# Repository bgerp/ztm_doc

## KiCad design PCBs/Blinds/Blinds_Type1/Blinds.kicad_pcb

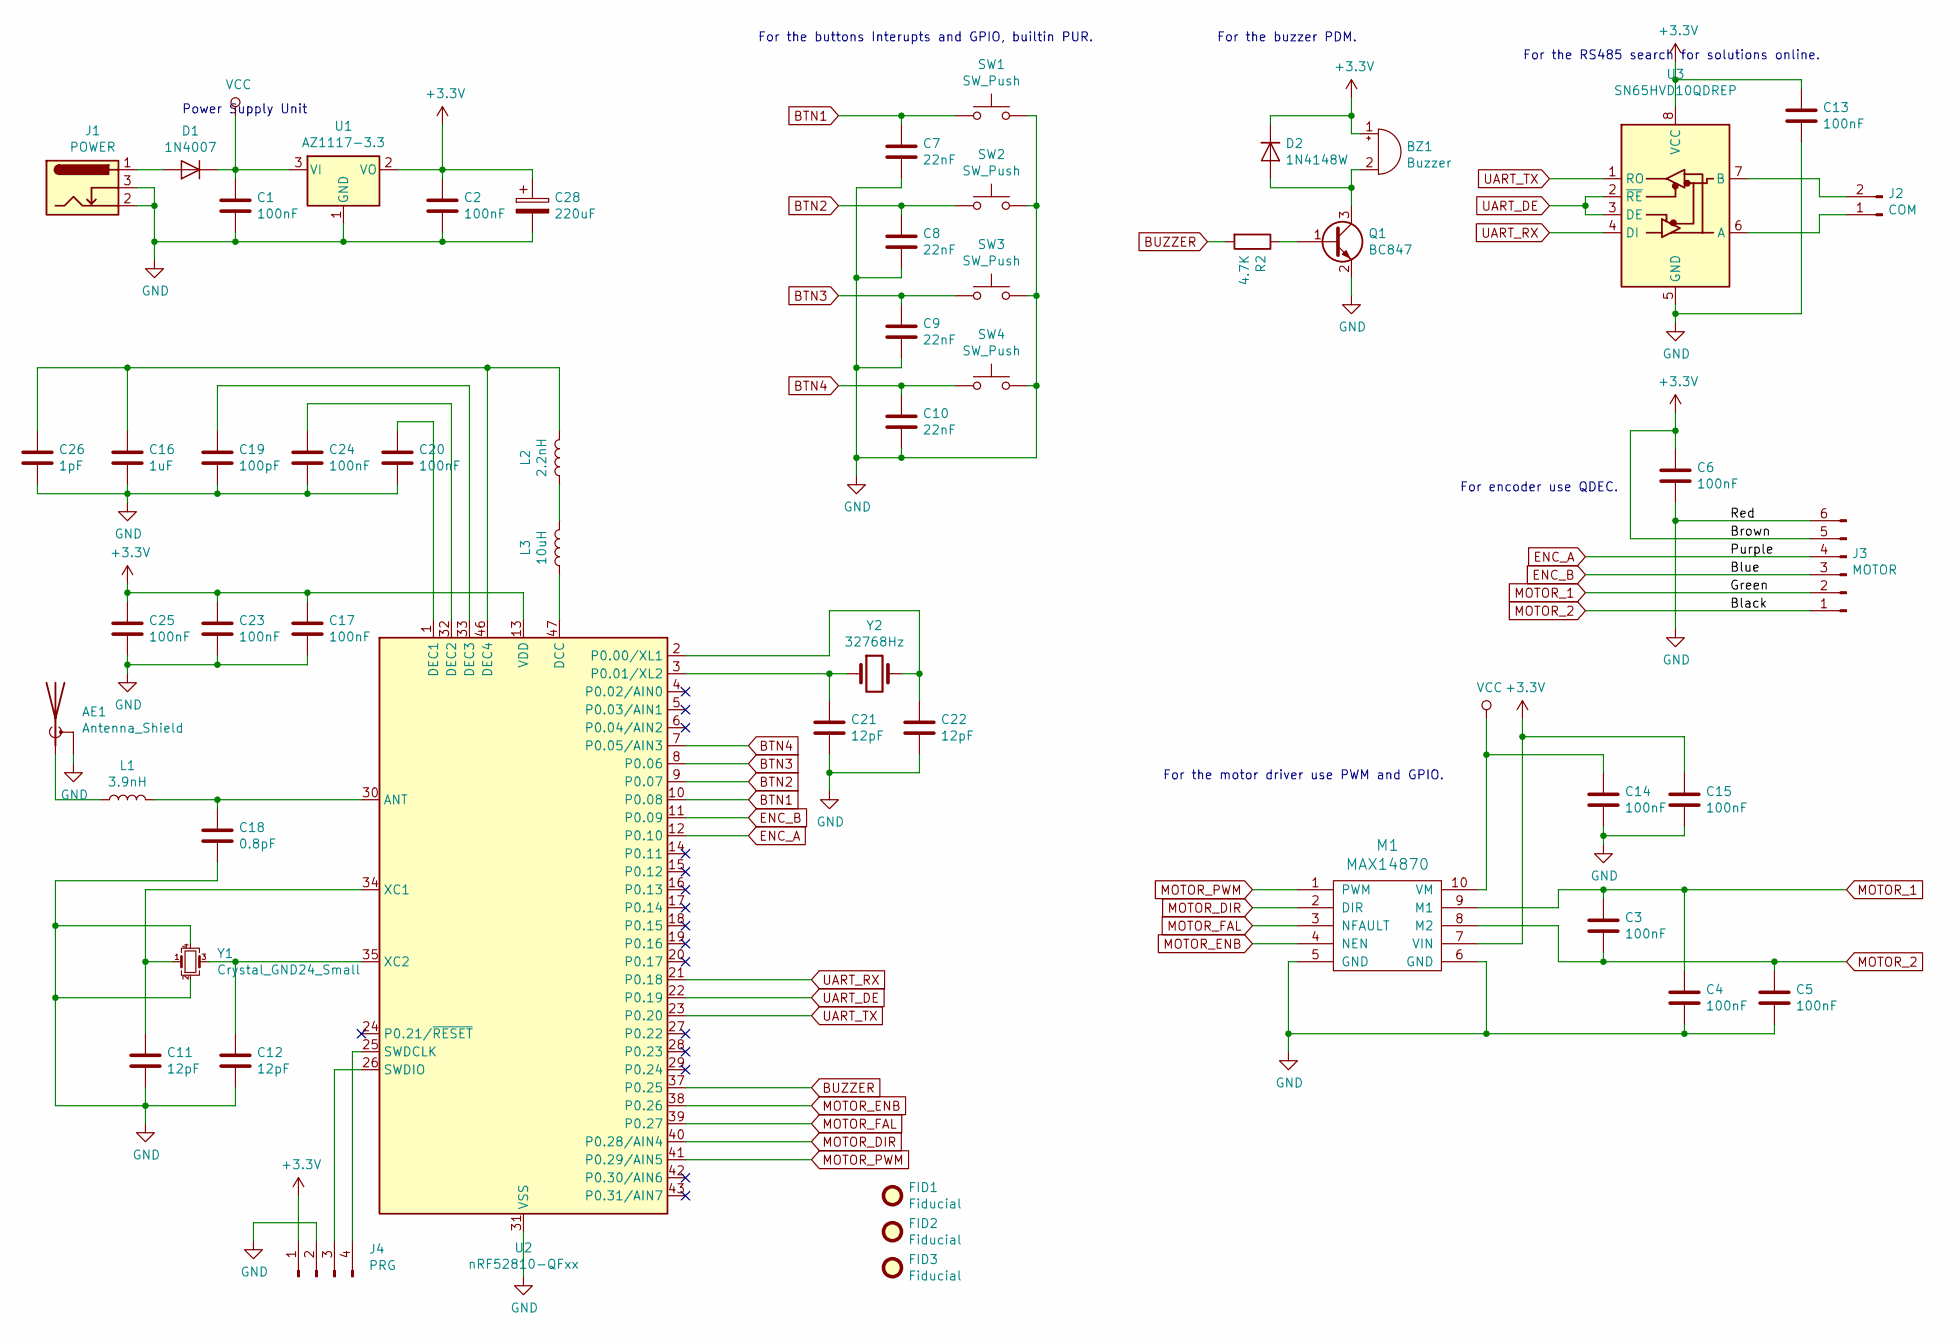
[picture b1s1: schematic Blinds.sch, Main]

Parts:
AE1: Antenna_Shield; Texas_SWRA117D_2.4GHz_Left
BZ1: Buzzer; MagneticBuzzer_Kingstate_KCG0601
C1, C2, C3, C4, C5, C6, C13, C14, C15, C23: 100nF; C_0603_1608Metric
C7, C8, C9, C10: 22nF; C_0603_1608Metric
C11, C12, C21, C22: 12pF; C_0402_1005Metric
C16: 1uF; C_0603_1608Metric
C17, C20, C24, C25: 100nF; C_0402_1005Metric
C18: 0.8pF; C_0402_1005Metric
C19: 100pF; C_0402_1005Metric
C26: 1pF; C_0402_1005Metric
C28: 220uF; CP_Elec_6.3x7.7
D1: 1N4007; D_SMA
D2: 1N4148W; D_SOD-123
FID1, FID2, FID3: Fiducial; Fiducial_0.5mm_Mask1mm
J1: POWER; BarrelJack_Horizontal
J2: COM; PinHeader_1x02_P2.54mm_Vertical
J3: MOTOR; JST_PH_B6B-PH-K_1x06_P2.00mm_Vertical
J4: PRG; PinHeader_1x04_P2.54mm_Vertical
L1: 3.9nH; R_0402_1005Metric
L2: 2.2nH; C_0402_1005Metric
L3: 10uH; C_0603_1608Metric
M1: MAX14870; DFN-12-1EP_3x3mm_P0.45mm_EP1.66x2.38mm
Q1: BC847; SOT-23
R2: 4.7K; R_0603_1608Metric
SW1, SW2, SW3, SW4: SW_Push; SW_SPST_CK_RS282G05A3
U1: AZ1117-3.3; SOT-89-3_Handsoldering
U2: nRF52810-QFxx; QFN-48-1EP_6x6mm_P0.4mm_EP4.66x4.66mm_ThermalVias
U3: SN65HVD10QDREP; SO-8_3.9x4.9mm_P1.27mm
Y1: Crystal_GND24_Small; Crystal_SMD_2016-4Pin_2.0x1.6mm
Y2: 32768Hz; Crystal_SMD_3215-2Pin_3.2x1.5mm

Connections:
+3V3: BZ1.1 (-), C2.1, C6.1, C13.1, C15.1, C17.1, C23.1, C25.1, C28.1, D2.1 (K), J3.5, J4.1, M1.7 (VIN), U1.2 (VO), U2.13 (VDD), U2.36 (VDD), U2.48 (VDD), U3.8 (VCC)
BTN1: C7.1, SW1.1, U2.10 (P0.08)
BTN2: C8.1, SW2.1, U2.9 (P0.07)
BTN3: C9.1, SW3.1, U2.8 (P0.06)
BTN4: C10.1, SW4.1, U2.7 (P0.05/AIN3)
BUZZER: R2.2, U2.37 (P0.25)
ENC_A: J3.4, U2.12 (P0.10)
ENC_B: J3.3, U2.11 (P0.09)
GND: AE1.2 (Shield), C1.2, C2.2, C4.2, C5.2, C6.2, C7.2, C8.2, C9.2, C10.2, C11.2, C12.2, C13.2, C14.2, C15.2, C16.2, C17.2, C18.2, C19.2, C20.2, C21.2, C22.2, C23.2, C24.2, C25.2, C26.2, C28.2, J1.2, J1.3, J3.6, J4.2, M1.5 (GND), M1.6 (GND), Q1.2 (E), SW1.2, SW2.2, SW3.2, SW4.2, U1.1 (GND), U2.31 (VSS), U2.45 (VSS), U2.49 (VSS), U3.5 (GND), Y1.2, Y1.4
MOTOR_1: C3.1, C4.1, J3.2, M1.9 (M1)
MOTOR_2: C3.2, C5.1, J3.1, M1.8 (M2)
MOTOR_DIR: M1.2 (DIR), U2.40 (P0.28/AIN4)
MOTOR_ENB: M1.4 (NEN), U2.38 (P0.26)
MOTOR_FAL: M1.3 (NFAULT), U2.39 (P0.27)
MOTOR_PWM: M1.1 (PWM), U2.41 (P0.29/AIN5)
unnamed: AE1.1 (A), L1.1
unnamed: BZ1.2 (+), D2.2 (A), Q1.3 (C)
unnamed: C11.1, U2.34 (XC1), Y1.1
unnamed: C12.1, U2.35 (XC2), Y1.3
unnamed: C16.1, C26.1, L2.2, U2.46 (DEC4)
unnamed: C18.1, L1.2, U2.30 (ANT)
unnamed: C19.1, U2.33 (DEC3)
unnamed: C20.1, U2.1 (DEC1)
unnamed: C21.1, U2.3 (P0.01/XL2), Y2.1
unnamed: C22.1, U2.2 (P0.00/XL1), Y2.2
unnamed: C24.1, U2.32 (DEC2)
unnamed: D1.2 (A), J1.1
unnamed: J2.1, U3.6 (A)
unnamed: J2.2, U3.7 (B)
unnamed: J4.3, U2.26 (SWDIO)
unnamed: J4.4, U2.25 (SWDCLK)
unnamed: L2.1, L3.2
unnamed: L3.1, U2.47 (DCC)
unnamed: Q1.1 (B), R2.1
UART_DE: U2.22 (P0.19), U3.2 (~RE), U3.3 (DE)
UART_RX: U2.21 (P0.18), U3.4 (DI)
UART_TX: U2.23 (P0.20), U3.1 (RO)
VCC: C1.1, C14.1, D1.1 (K), M1.10 (VM), U1.3 (VI)

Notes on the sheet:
For encoder use QDEC.
For the motor driver use PWM and GPIO.
For the buzzer PDM.
For the buttons Interupts and GPIO, builtin PUR.
For the RS485 search for solutions online.
Power Supply Unit

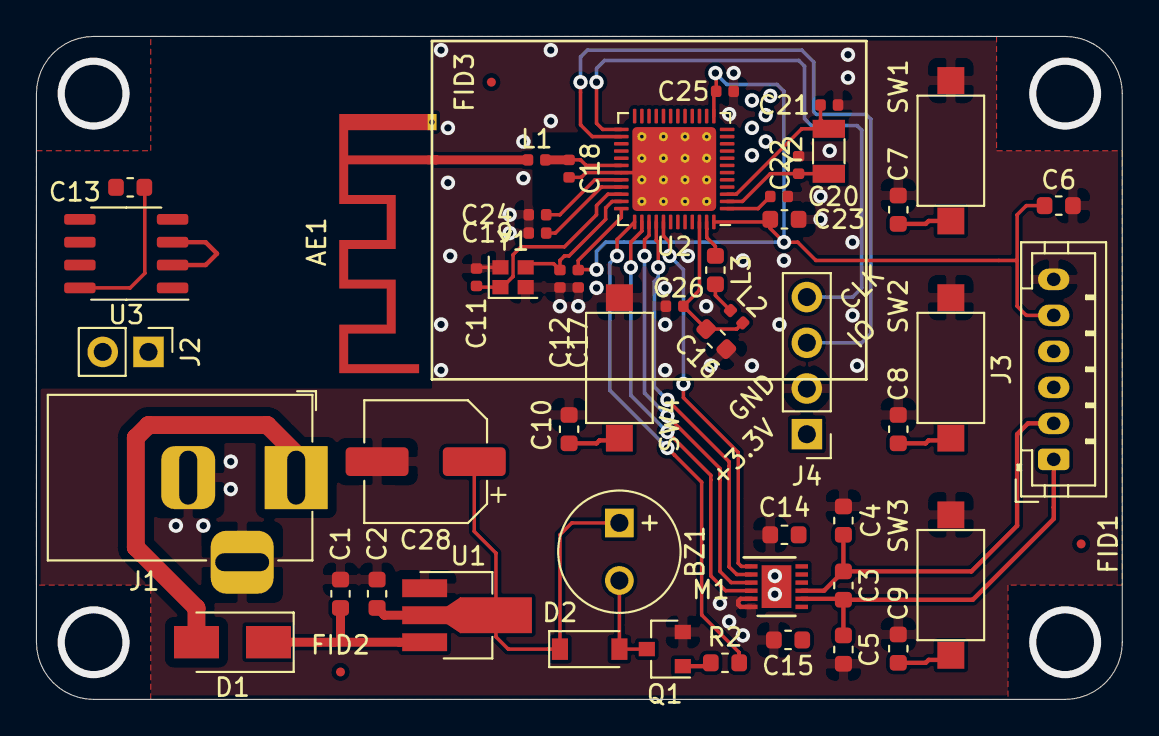
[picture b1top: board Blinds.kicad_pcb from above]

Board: 2 copper layers, 60.3 x 36.8 mm, 53 parts (0 on the bottom side), 38 nets.

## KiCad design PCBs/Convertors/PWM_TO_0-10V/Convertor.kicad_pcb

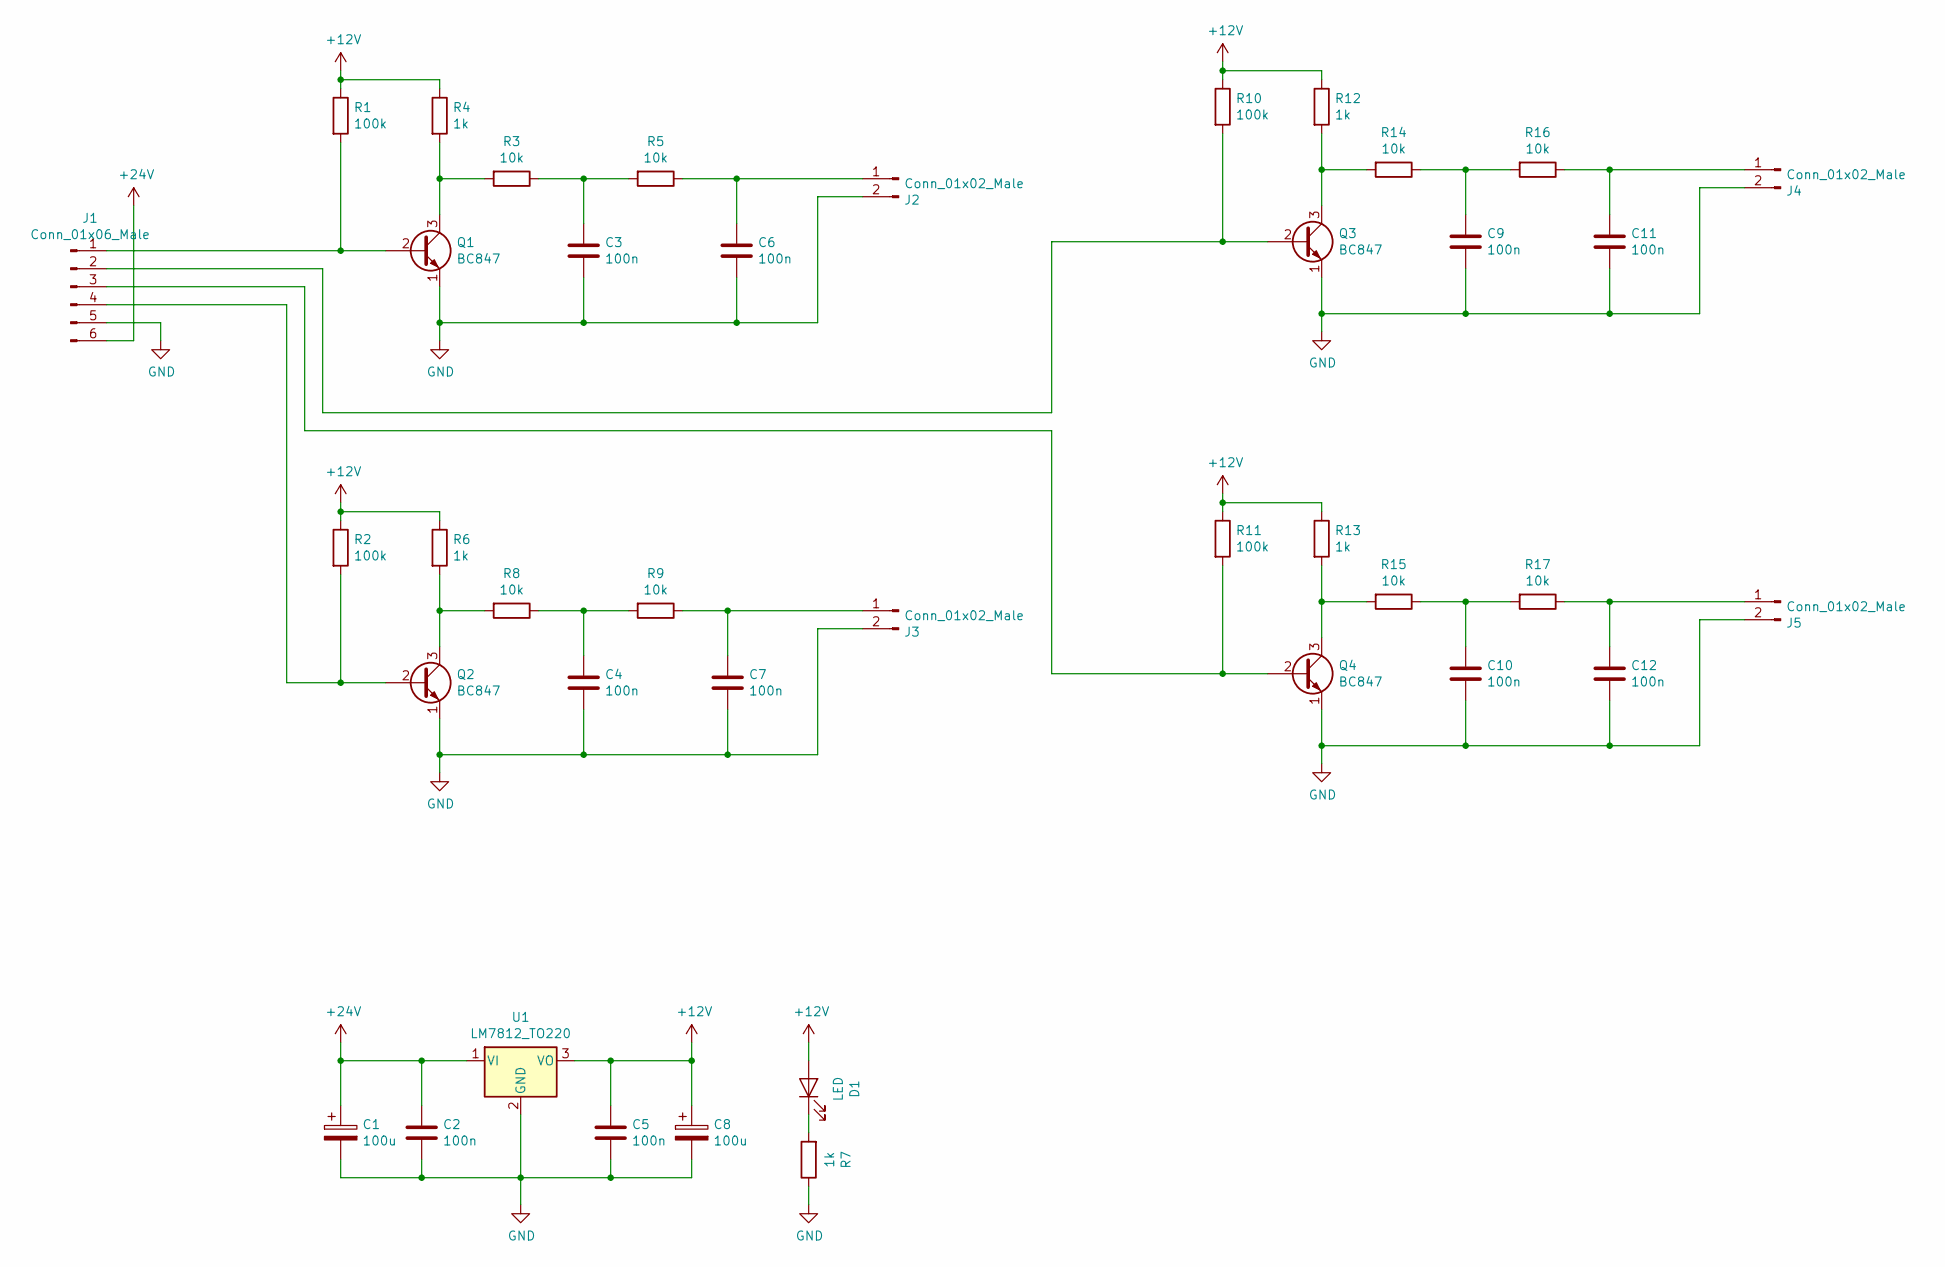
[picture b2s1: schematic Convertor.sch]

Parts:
C1, C8: 100u; CP_Elec_8x11.9
C2, C3, C4, C5, C6, C7, C9, C10, C11, C12: 100n; C_0805_2012Metric
D1: LED; LED_0805_2012Metric
J1: Conn_01x06_Male; PhoenixContact_MSTBA_2,5_6-G-5,08_1x06_P5.08mm_Horizontal
J2, J3, J4, J5: Conn_01x02_Male; PhoenixContact_MSTBA_2,5_2-G-5,08_1x02_P5.08mm_Horizontal
Q1, Q2, Q3, Q4: BC847; SOT-23
R1, R2, R10, R11: 100k; R_0805_2012Metric
R3, R5, R8, R9, R14, R15, R16, R17: 10k; R_0805_2012Metric
R4, R6, R7, R12, R13: 1k; R_0805_2012Metric
U1: LM7812_TO220; TO-220-3_Horizontal_TabDown

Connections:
+12V: C5.1, C8.1, D1.2 (A), R1.1, R2.1, R4.1, R6.1, R10.1, R11.1, R12.1, R13.1, U1.3 (VO)
+24V: C1.1, C2.1, J1.6, U1.1 (VI)
GND: C1.2, C2.2, C3.2, C4.2, C5.2, C6.2, C7.2, C8.2, C9.2, C10.2, C11.2, C12.2, J1.5, J2.2, J3.2, J4.2, J5.2, Q1.1 (E), Q2.1 (E), Q3.1 (E), Q4.1 (E), R7.1, U1.2 (GND)
unnamed: C3.1, R3.1, R5.2
unnamed: C4.1, R8.1, R9.2
unnamed: C6.1, J2.1, R5.1
unnamed: C7.1, J3.1, R9.1
unnamed: C9.1, R14.1, R16.2
unnamed: C10.1, R15.1, R17.2
unnamed: C11.1, J4.1, R16.1
unnamed: C12.1, J5.1, R17.1
unnamed: D1.1 (K), R7.2
unnamed: J1.1, Q1.2 (B), R1.2
unnamed: J1.2, Q3.2 (B), R10.2
unnamed: J1.3, Q4.2 (B), R11.2
unnamed: J1.4, Q2.2 (B), R2.2
unnamed: Q1.3 (C), R3.2, R4.2
unnamed: Q2.3 (C), R6.2, R8.2
unnamed: Q3.3 (C), R12.2, R14.2
unnamed: Q4.3 (C), R13.2, R15.2

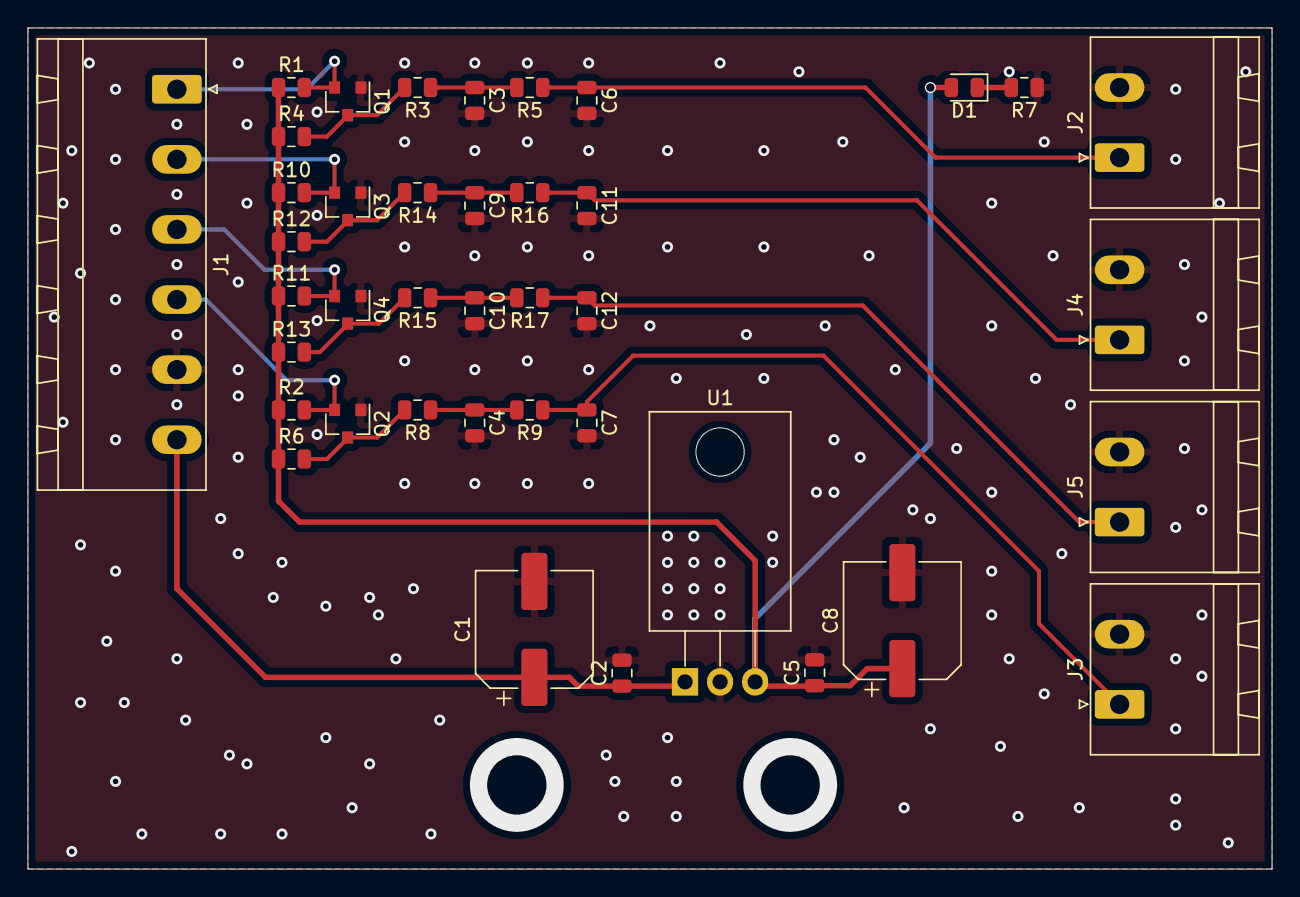
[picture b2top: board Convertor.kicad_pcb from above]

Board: 2 copper layers, 90.2 x 61.0 mm, 40 parts (0 on the bottom side), 20 nets.

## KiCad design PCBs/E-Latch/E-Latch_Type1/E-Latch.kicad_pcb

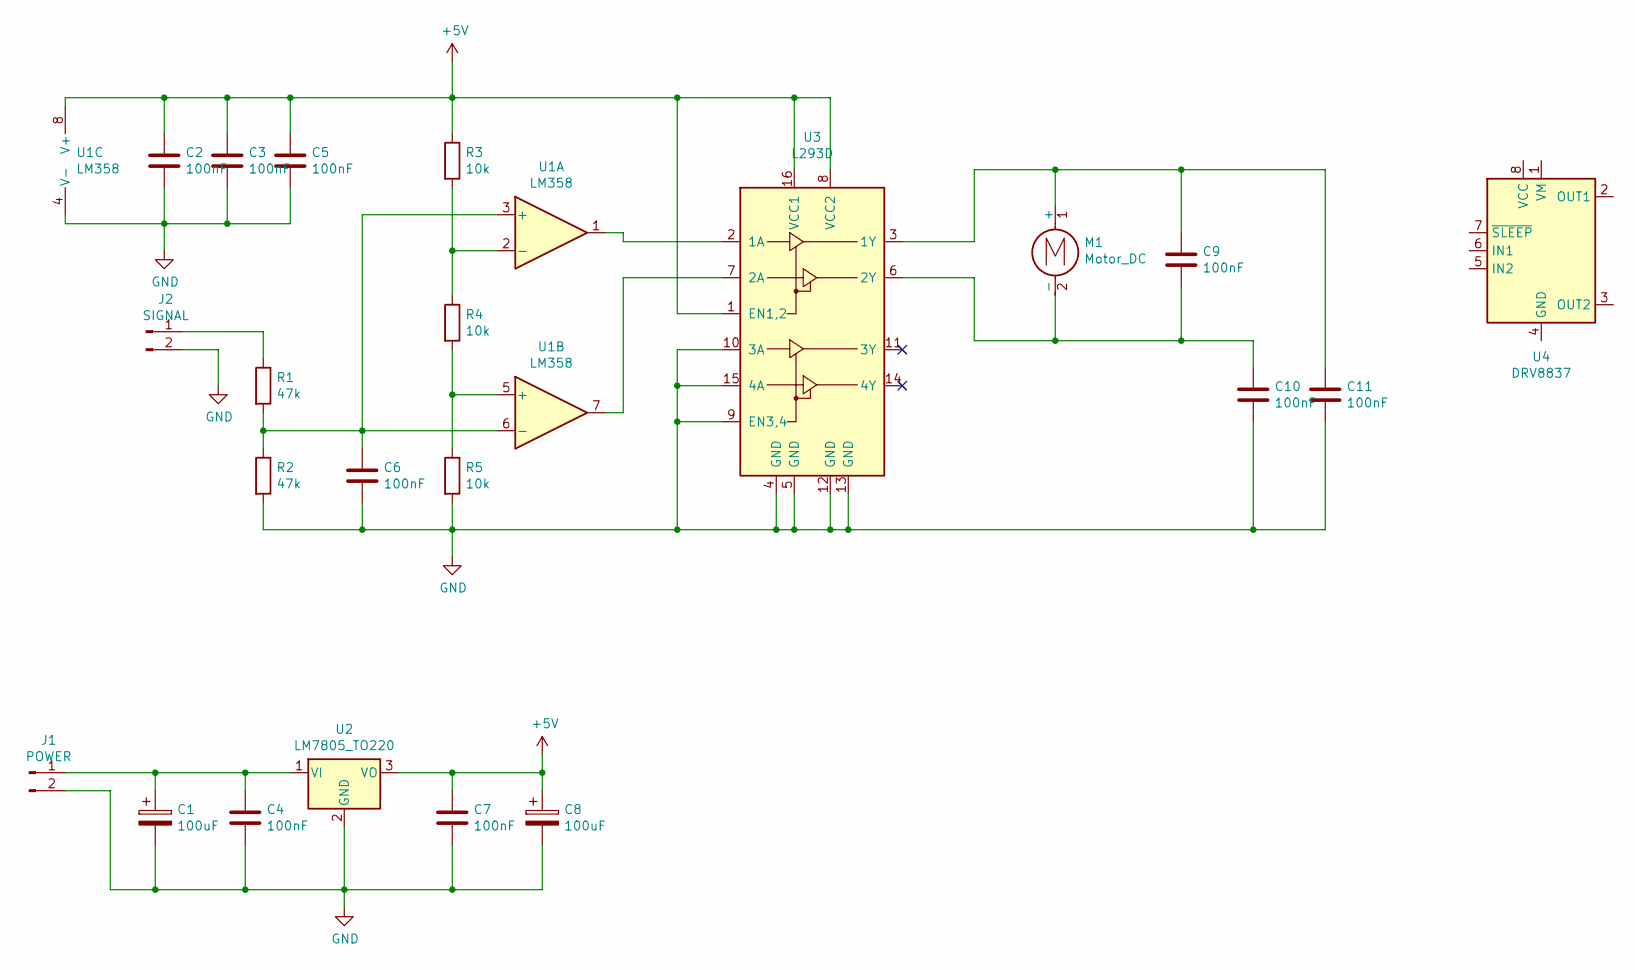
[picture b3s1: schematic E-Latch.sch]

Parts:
C1, C8: 100uF; CP_Elec_8x11.9
C2, C3, C4, C5, C6, C7, C9, C10, C11: 100nF; C_0805_2012Metric
J1: POWER; PhoenixContact_MSTBA_2,5_2-G-5,08_1x02_P5.08mm_Horizontal
J2: SIGNAL; PhoenixContact_MSTBA_2,5_2-G-5,08_1x02_P5.08mm_Horizontal
M1: Motor_DC; PhoenixContact_MSTBA_2,5_2-G-5,08_1x02_P5.08mm_Horizontal
R1, R2: 47k; R_0805_2012Metric
R3, R4, R5: 10k; R_0805_2012Metric
U1: LM358; SOIC-8_3.9x4.9mm_P1.27mm
U2: LM7805_TO220; TO-220-3_Vertical
U3: L293D; DIP-16_W7.62mm
U4: DRV8837; WSON-8-1EP_2x2mm_P0.5mm_EP0.9x1.6mm

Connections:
+5V: C2.1, C3.1, C5.1, C7.1, C8.1, R3.1, U1.8 (V+), U2.3 (VO), U3.1 (EN1,2), U3.8 (VCC2), U3.16 (VCC1)
GND: C1.2, C2.2, C3.2, C4.2, C5.2, C6.2, C7.2, C8.2, C10.2, C11.2, J1.2, J2.2, R2.2, R5.2, U1.4 (V-), U2.2 (GND), U3.4 (GND), U3.5 (GND), U3.9 (EN3,4), U3.10 (3A), U3.12 (GND), U3.13 (GND), U3.15 (4A)
unnamed: C1.1, C4.1, J1.1, U2.1 (VI)
unnamed: C6.1, R1.2, R2.1, U1.3 (+), U1.6 (-)
unnamed: C9.2, C10.1, M1.2 (-), U3.6 (2Y)
unnamed: C9.1, C11.1, M1.1 (+), U3.3 (1Y)
unnamed: J2.1, R1.1
unnamed: R3.2, R4.1, U1.2 (-)
unnamed: R4.2, R5.1, U1.5 (+)
unnamed: U1.1, U3.2 (1A)
unnamed: U1.7, U3.7 (2A)
unnamed: U4.4 (GND), U4.9 (GND)

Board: 2 copper layers, 23 parts (0 on the bottom side), 12 nets, no tracks yet.

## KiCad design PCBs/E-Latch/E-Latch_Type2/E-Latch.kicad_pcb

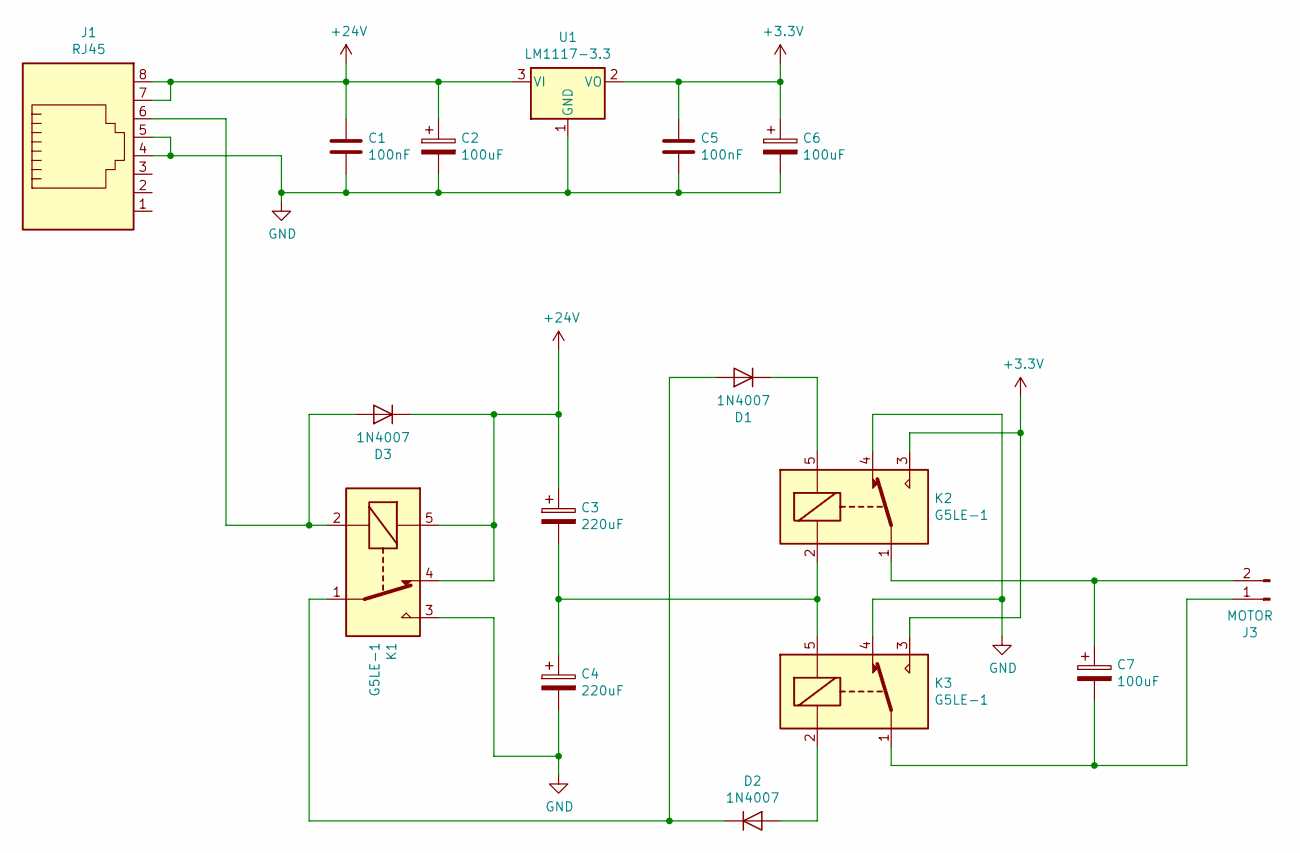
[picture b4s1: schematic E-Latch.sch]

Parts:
C1, C5: 100nF; C_0805_2012Metric
C2, C6: 100uF; CP_Radial_D8.0mm_P3.50mm
C3, C4: 220uF; CP_Radial_D8.0mm_P3.50mm
C7: 100uF; C_0805_2012Metric
D1, D2, D3: 1N4007; D_SMA
J1: RJ45; RJ45_Amphenol_54602-x08_Horizontal
J3: MOTOR; PhoenixContact_MSTBVA_2,5_2-G-5,08_1x02_P5.08mm_Vertical
K1, K2, K3: G5LE-1; Relay_SPDT_Omron-G5LE-1
U1: LM1117-3.3; SOT-89-3_Handsoldering

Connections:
+3V3: C5.1, C6.1, K2.3, K3.3, U1.2 (VO)
+24V: C1.1, C2.1, C3.1, D3.1 (K), J1.7, J1.8, K1.4, K1.5, U1.3 (VI)
GND: C1.2, C2.2, C4.2, C5.2, C6.2, J1.4, J1.5, K1.3, K2.4, K3.4, U1.1 (GND)
unnamed: C3.2, C4.1, K2.2, K3.5
unnamed: C7.1, J3.2, K2.1
unnamed: C7.2, J3.1, K3.1
unnamed: D1.1 (K), K2.5
unnamed: D1.2 (A), D2.1 (K), K1.1
unnamed: D2.2 (A), K3.2
unnamed: D3.2 (A), J1.6, K1.2

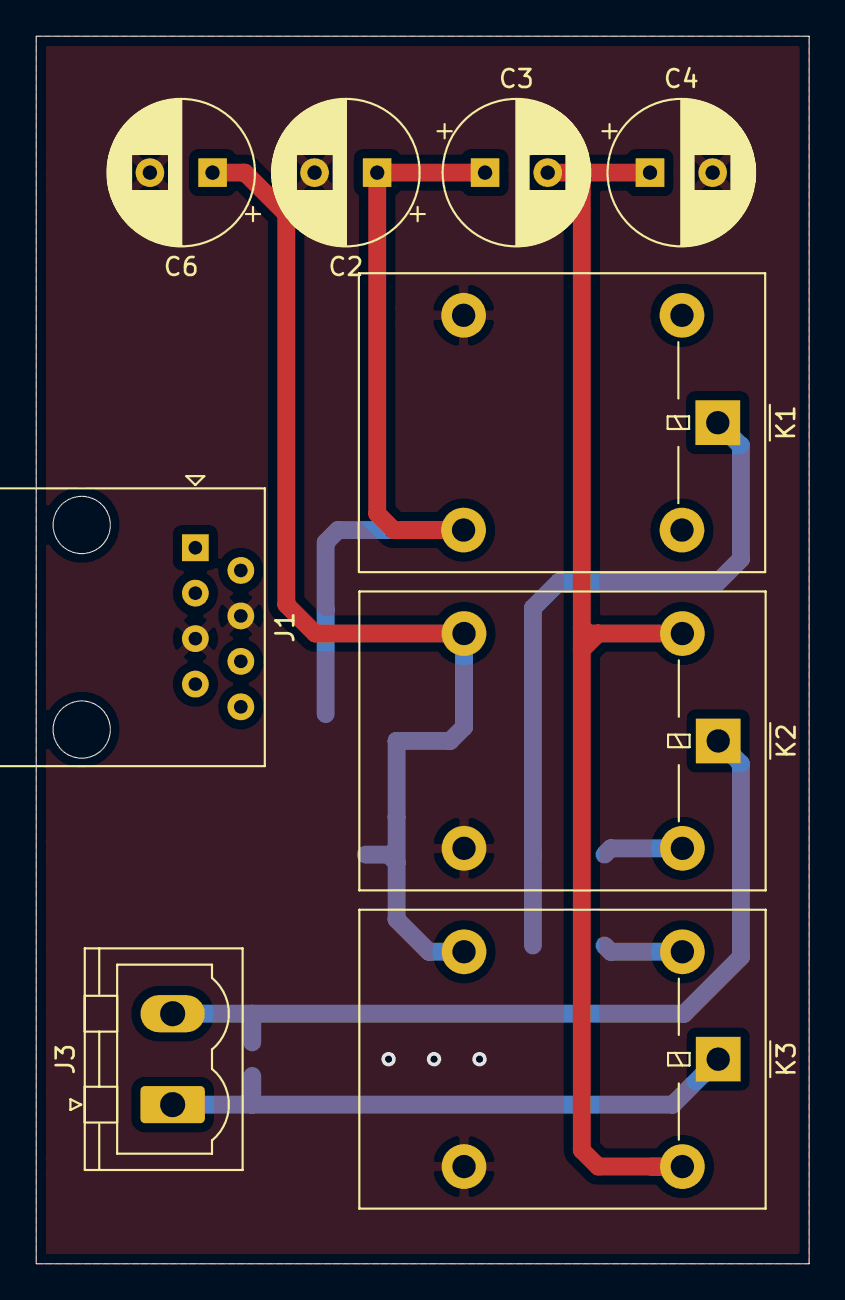
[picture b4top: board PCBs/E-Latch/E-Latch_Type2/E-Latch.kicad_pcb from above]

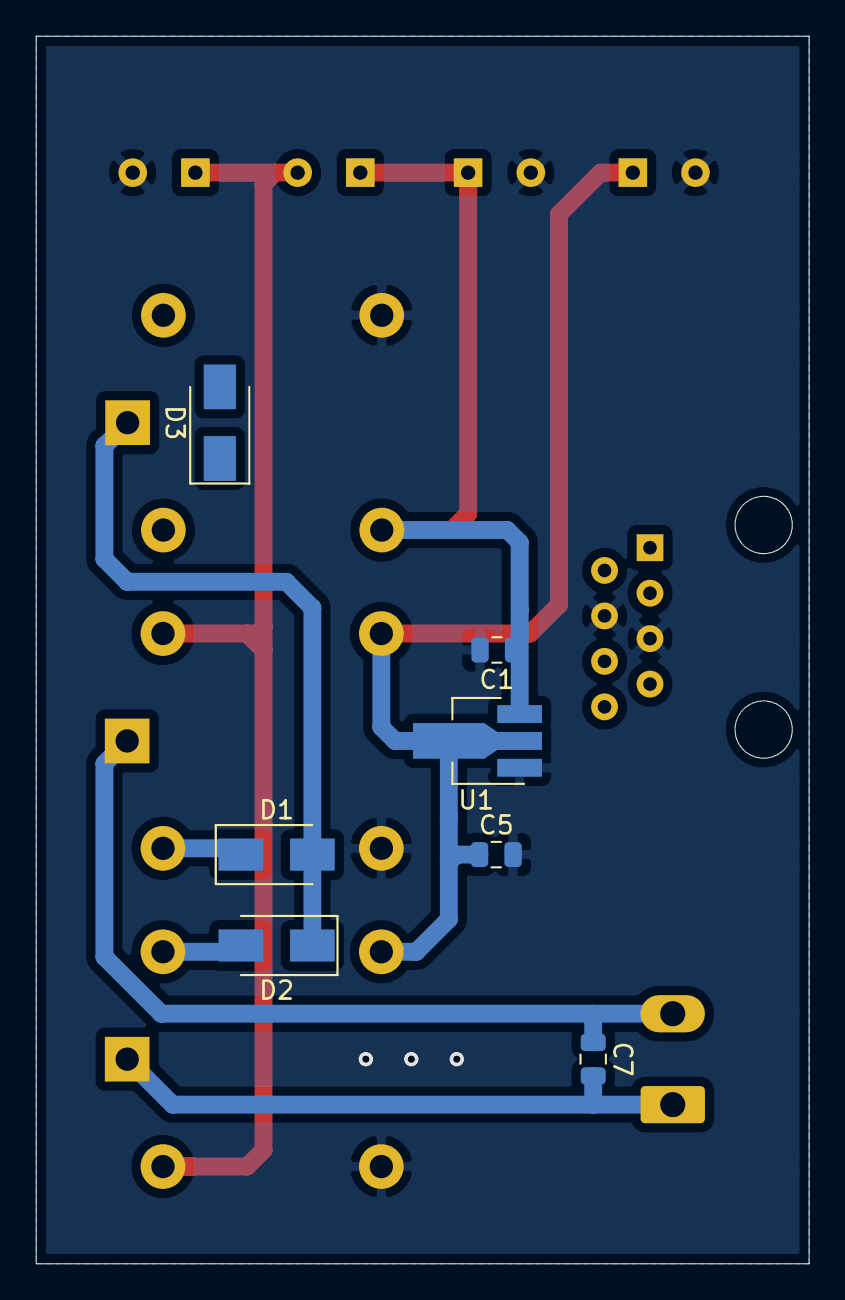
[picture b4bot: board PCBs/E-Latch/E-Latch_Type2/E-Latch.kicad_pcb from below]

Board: 2 copper layers, 43.2 x 68.6 mm, 16 parts (7 on the bottom side), 10 nets.

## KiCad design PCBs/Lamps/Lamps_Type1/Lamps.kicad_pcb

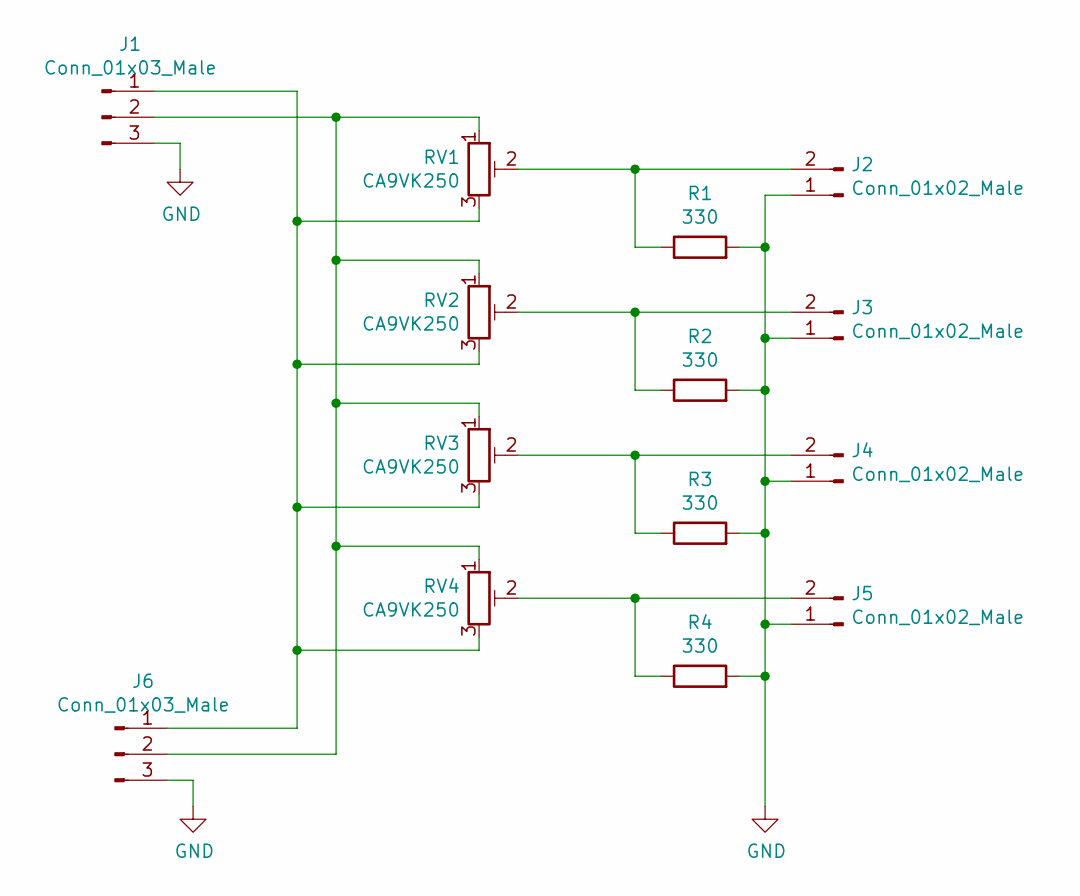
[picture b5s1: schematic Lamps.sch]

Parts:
J1, J6: Conn_01x03_Male; PhoenixContact_MSTBVA_2,5_3-G-5,08_1x03_P5.08mm_Vertical
J2, J3, J4, J5: Conn_01x02_Male; PhoenixContact_MSTBVA_2,5_2-G-5,08_1x02_P5.08mm_Vertical
R1, R2, R3, R4: 330; R_Axial_DIN0207_L6.3mm_D2.5mm_P2.54mm_Vertical
RV1, RV2, RV3, RV4: CA9VK250; Potentiometer_ACP_CA9-V10_Vertical_Hole

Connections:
GND: J1.3, J2.1, J3.1, J4.1, J5.1, J6.3, R1.2, R2.2, R3.2, R4.2
unnamed: J1.1, J6.1, RV1.3, RV2.3, RV3.3, RV4.3
unnamed: J1.2, J6.2, RV1.1, RV2.1, RV3.1, RV4.1
unnamed: J2.2, R1.1, RV1.2
unnamed: J3.2, R2.1, RV2.2
unnamed: J4.2, R3.1, RV3.2
unnamed: J5.2, R4.1, RV4.2

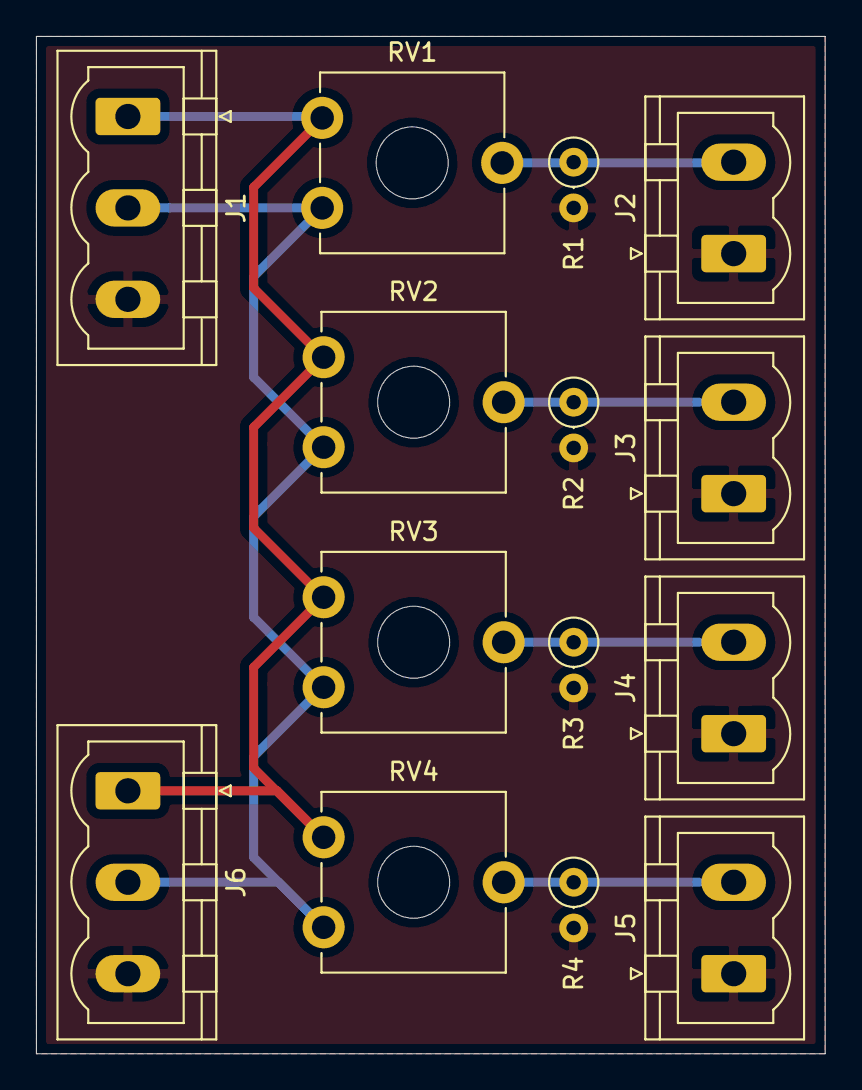
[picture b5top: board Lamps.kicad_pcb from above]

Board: 2 copper layers, 43.8 x 56.5 mm, 14 parts (0 on the bottom side), 7 nets.
